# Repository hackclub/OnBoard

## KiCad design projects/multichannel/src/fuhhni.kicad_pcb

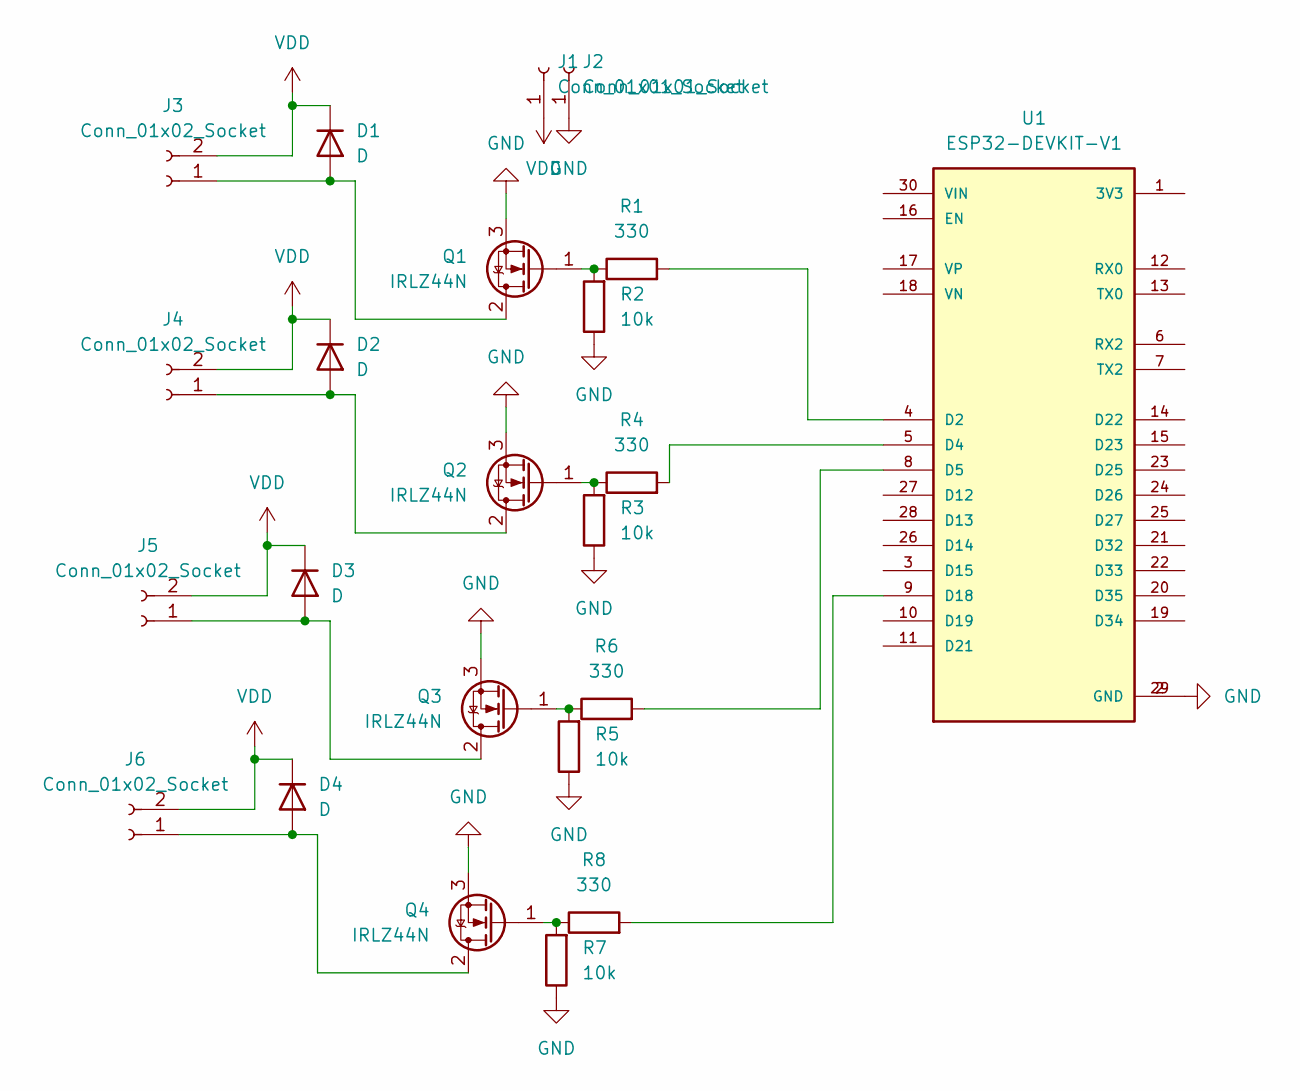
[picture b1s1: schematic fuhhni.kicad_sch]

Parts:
D1, D2, D3, D4: D; D_A-405_P7.62mm_Horizontal
J1, J2: Conn_01x01_Socket; PinSocket_1x01_P2.54mm_Vertical
J3, J4, J5, J6: Conn_01x02_Socket; PinSocket_1x02_P2.54mm_Vertical
Q1, Q2, Q3, Q4: IRLZ44N; TO-220-3_Vertical
R1, R4, R6, R8: 330; R_Axial_DIN0207_L6.3mm_D2.5mm_P7.62mm_Horizontal
R2, R3, R5, R7: 10k; R_Axial_DIN0207_L6.3mm_D2.5mm_P7.62mm_Horizontal
U1: ESP32-DEVKIT-V1; MODULE_ESP32_DEVKIT_V1; PARTREV N/A

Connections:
GND: J2.1, Q1.3 (S), Q2.3 (S), Q3.3 (S), Q4.3 (S), R2.1, R3.1, R5.1, R7.1, U1.2 (GND), U1.29 (GND)
unnamed: D1.2 (A), J3.1, Q1.2 (D)
unnamed: D2.2 (A), J4.1, Q2.2 (D)
unnamed: D3.2 (A), J5.1, Q3.2 (D)
unnamed: D4.2 (A), J6.1, Q4.2 (D)
unnamed: Q1.1 (G), R1.1, R2.2
unnamed: Q2.1 (G), R3.2, R4.1
unnamed: Q3.1 (G), R5.2, R6.1
unnamed: Q4.1 (G), R7.2, R8.1
unnamed: R1.2, U1.4 (D2)
unnamed: R4.2, U1.5 (D4)
unnamed: R6.2, U1.8 (D5)
unnamed: R8.2, U1.9 (D18)
VDD: D1.1 (K), D2.1 (K), D3.1 (K), D4.1 (K), J1.1, J3.2, J4.2, J5.2, J6.2

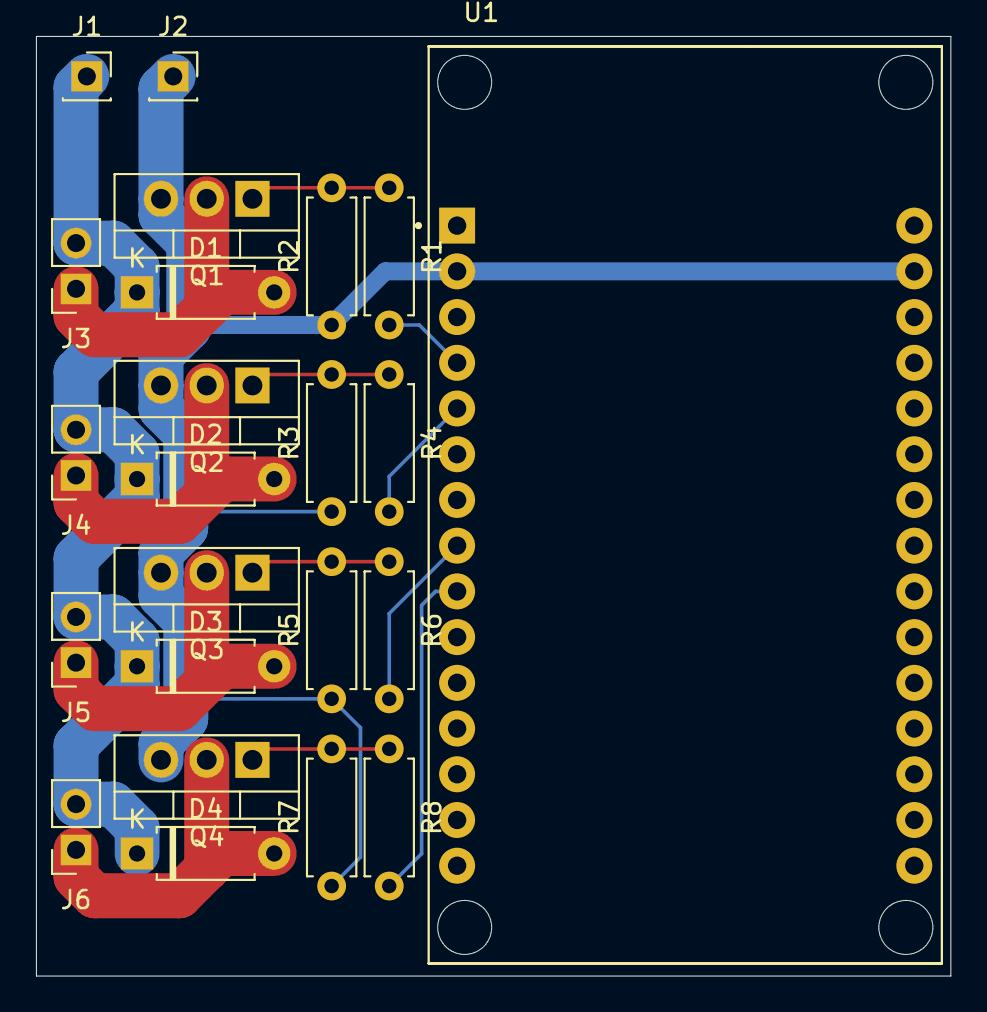
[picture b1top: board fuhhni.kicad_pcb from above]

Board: 2 copper layers, 50.8 x 52.2 mm, 23 parts (0 on the bottom side), 14 nets.

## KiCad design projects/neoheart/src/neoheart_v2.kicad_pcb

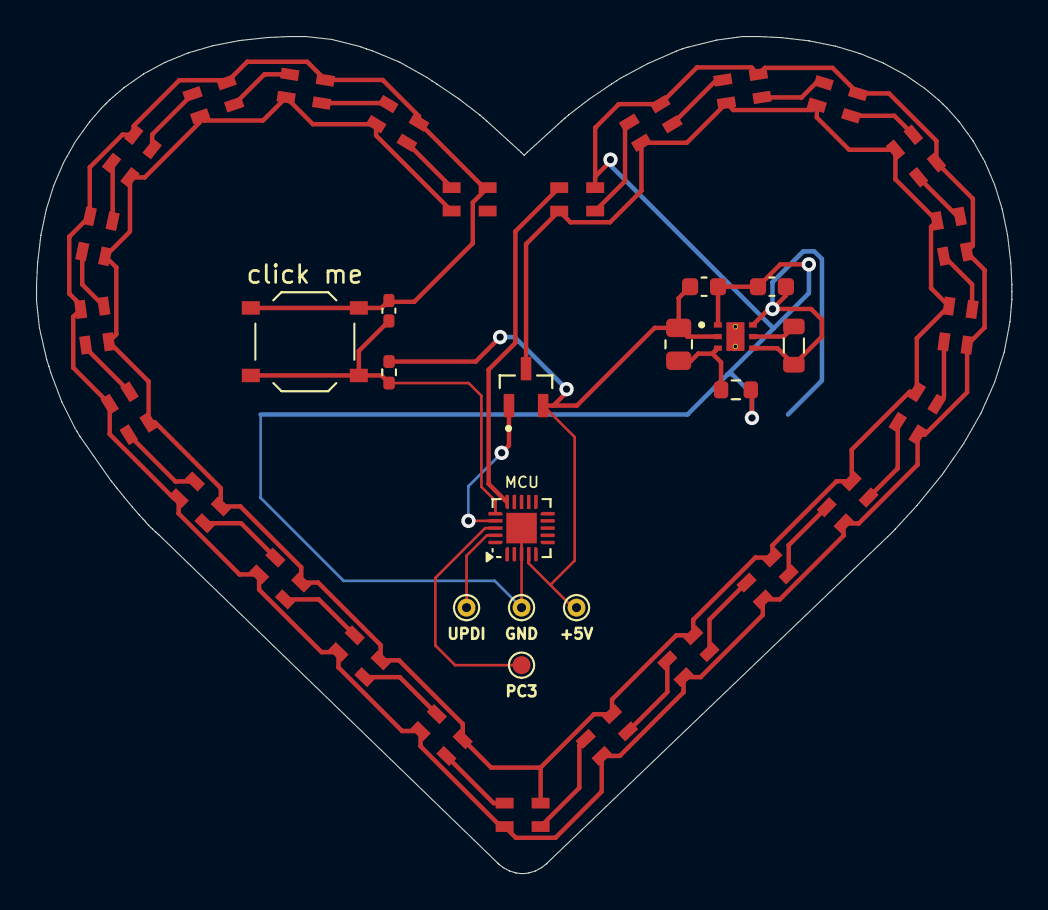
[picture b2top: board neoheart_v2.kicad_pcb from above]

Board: 2 copper layers, 54.2 x 46.5 mm, 41 parts (1 on the bottom side), 35 nets.

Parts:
+5V: +5V; TestPoint_THTPad_D1.0mm_Drill0.5mm
BATTERY (CR2032): Battery; BatteryHolder_Keystone_1060_1x2032
C2: 100nF; C_0402_1005Metric_Pad0.74x0.62mm_HandSolder
C3, C4: 22μF; C_0603_1608Metric
D1, D2, D3, D4, D5, D6, D7, D8, D9, D10, D11, D12, D13, D14, D15, D16, D17, D18, D19, D20, D21, D22, D23, D24, D25: SK6805; LED_SK6805_PLCC4_2.4x2.7mm_P1.3mm
GND: GND; TestPoint_THTPad_D1.0mm_Drill0.5mm
L1: 4,7μH; L_0805_2012Metric
MCU: ATtiny816-M; VQFN-20-1EP_3x3mm_P0.4mm_EP1.7x1.7mm
PC3: PC3; TestPoint_Pad_D1.0mm
Q1: IRLML2502; SOT95P237X112-3N
R1: 1K; R_0402_1005Metric_Pad0.72x0.64mm_HandSolder
R2: 180kΩ; R_0805_2012Metric
R3: 1,5MΩ; R_0603_1608Metric
U2: TPS61240TDRVRQ1; SON65P200X200X80-7N
UPDI: UPDI; TestPoint_THTPad_D1.0mm_Drill0.5mm
click me: SW_SPST; SW_Push_1P1T_XKB_TS-1187A

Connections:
+3V0: BATTERY (CR2032).1 (+), C3.1, L1.1, U2.4 (EN), U2.6 (VIN)
+5V: +5V.1, C4.1, MCU.4 (VCC), Q1.2, R1.1, R2.2, U2.2 (VOUT)
/IO_LEDS: D1.3 (DIN), MCU.15 (PC0)
/IO_MOSFET: MCU.17 (PC2), Q1.1
/LED5V: D1.4 (VDD), D2.4 (VDD), D3.4 (VDD), D4.4 (VDD), D5.4 (VDD), D6.4 (VDD), D7.4 (VDD), D8.4 (VDD), D9.4 (VDD), D10.4 (VDD), D11.4 (VDD), D12.4 (VDD), D13.4 (VDD), D14.4 (VDD), D15.4 (VDD), D16.4 (VDD), D17.4 (VDD), D18.4 (VDD), D19.4 (VDD), D20.4 (VDD), D21.4 (VDD), D22.4 (VDD), D23.4 (VDD), D24.4 (VDD), D25.4 (VDD), Q1.3
/PC3: MCU.18 (PC3), PC3.1
/SW_ANIM: C2.1, MCU.16 (PC1), R1.2, click me.2 (B)
/UPDI: MCU.19 (~RESET/PA0), UPDI.1
GND: BATTERY (CR2032).2 (-), C2.2, C3.2, C4.2, D1.2 (VSS), D2.2 (VSS), D3.2 (VSS), D4.2 (VSS), D5.2 (VSS), D6.2 (VSS), D7.2 (VSS), D8.2 (VSS), D9.2 (VSS), D10.2 (VSS), D11.2 (VSS), D12.2 (VSS), D13.2 (VSS), D14.2 (VSS), D15.2 (VSS), D16.2 (VSS), D17.2 (VSS), D18.2 (VSS), D19.2 (VSS), D20.2 (VSS), D21.2 (VSS), D22.2 (VSS), D23.2 (VSS), D24.2 (VSS), D25.2 (VSS), GND.1, MCU.3 (GND), MCU.21 (GND), R3.1, U2.1 (GND), click me.1 (A)
unnamed: D1.1 (DOUT), D4.3 (DIN)
unnamed: D2.3 (DIN), D24.1 (DOUT)
unnamed: D2.1 (DOUT), D5.3 (DIN)
unnamed: D3.1 (DOUT), D6.3 (DIN)
unnamed: D4.1 (DOUT), D7.3 (DIN)
unnamed: D5.1 (DOUT), D8.3 (DIN)
unnamed: D6.1 (DOUT), D9.3 (DIN)
unnamed: D7.1 (DOUT), D10.3 (DIN)
unnamed: D10.1 (DOUT), D13.3 (DIN)
unnamed: D8.1 (DOUT), D11.3 (DIN)
unnamed: D11.1 (DOUT), D14.3 (DIN)
unnamed: D9.1 (DOUT), D12.3 (DIN)
unnamed: D12.1 (DOUT), D15.3 (DIN)
unnamed: D13.1 (DOUT), D16.3 (DIN)
unnamed: D14.1 (DOUT), D17.3 (DIN)
unnamed: D16.1 (DOUT), D18.3 (DIN)
unnamed: D17.1 (DOUT), D19.3 (DIN)
unnamed: D18.1 (DOUT), D20.3 (DIN)
unnamed: D19.1 (DOUT), D21.3 (DIN)
unnamed: D20.1 (DOUT), D22.3 (DIN)
unnamed: D21.1 (DOUT), D23.3 (DIN)
unnamed: D22.1 (DOUT), D24.3 (DIN)
unnamed: D23.1 (DOUT), D25.3 (DIN)
unnamed: D3.3 (DIN), D25.1 (DOUT)
unnamed: R2.1, R3.2, U2.3 (FB)
unnamed: L1.2, U2.5 (L)

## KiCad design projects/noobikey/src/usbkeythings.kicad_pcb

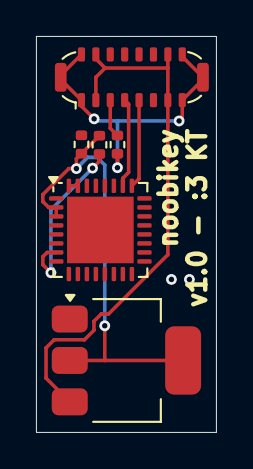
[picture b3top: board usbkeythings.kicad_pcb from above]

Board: 2 copper layers, 10.0 x 22.0 mm, 6 parts (0 on the bottom side), 8 nets.

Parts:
P1: USB_C_Plug_USB2.0; USB_C_Plug_ShenzhenJingTuoJin_918-118A2021Y40002_Vertical
R1: 5.1; R_0402_1005Metric
R2, R3: 10; R_0402_1005Metric
U1: ESP32-C3; QFN-32-1EP_5x5mm_P0.5mm_EP3.7x3.7mm
U2: AMS1117-3.3; SOT-223-3_TabPin2

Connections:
+3.3V: R2.2, R3.1, U1.2 (VDD3P3), U1.3 (VDD3P3), U2.2 (VO)
GND: P1.A1 (GND), P1.A12 (GND), P1.B1 (GND), P1.B12 (GND), P1.S1 (SHIELD), R1.1, U1.33 (GND)
unnamed: P1.A5 (CC), R1.2
unnamed: P1.A6 (D+), U1.26 (GPIO19)
unnamed: P1.A7 (D-), U1.25 (GPIO18)
unnamed: R2.1, U1.7 (CHIP_EN)
unnamed: U1.31 (VDDA), U1.32 (VDDA)
unnamed: P1.A4 (VBUS), P1.A9 (VBUS), P1.B4 (VBUS), P1.B9 (VBUS), U2.3 (VI)

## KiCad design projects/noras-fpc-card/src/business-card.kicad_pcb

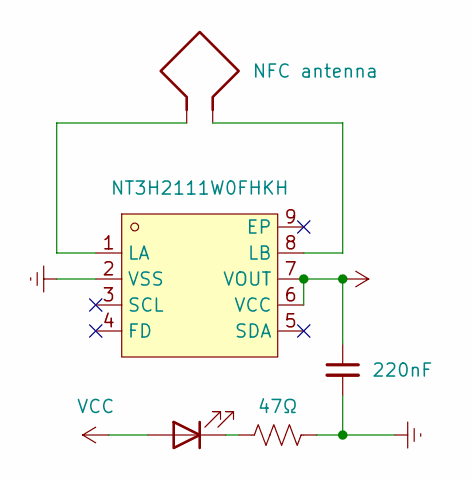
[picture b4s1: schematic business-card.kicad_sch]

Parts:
AE1: NFC antenna; nfc_ant
C1: 220nF; C_0603_1608Metric_Pad1.08x0.95mm_HandSolder
D1: LED; LED_0603_1608Metric_Pad1.05x0.95mm_HandSolder
R1: 47Ω; R_0603_1608Metric_Pad0.98x0.95mm_HandSolder
U1: NT3H2111W0FHKH; XQFN-8_L1.6-W1.6-P0.50-BL; LCSC Part C710403

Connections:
GND: C1.2, R1.2, U1.2 (VSS)
unnamed: D1.1 (K), R1.1
unnamed: AE1.1, U1.1 (LA)
unnamed: AE1.2, U1.8 (LB)
VCC: C1.1, D1.2 (A), U1.6 (VCC), U1.7 (VOUT)

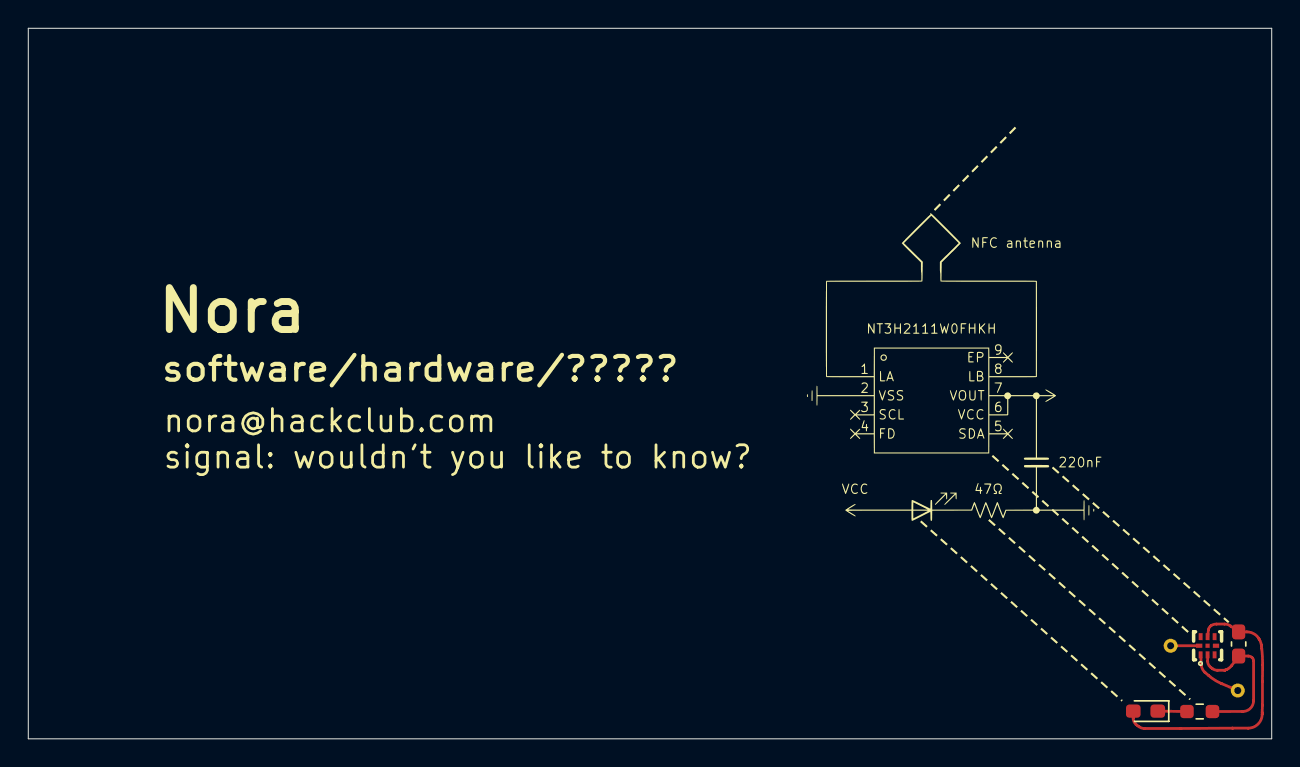
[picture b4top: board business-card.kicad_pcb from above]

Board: 2 copper layers, 88.9 x 50.8 mm, 5 parts (1 on the bottom side), 5 nets.

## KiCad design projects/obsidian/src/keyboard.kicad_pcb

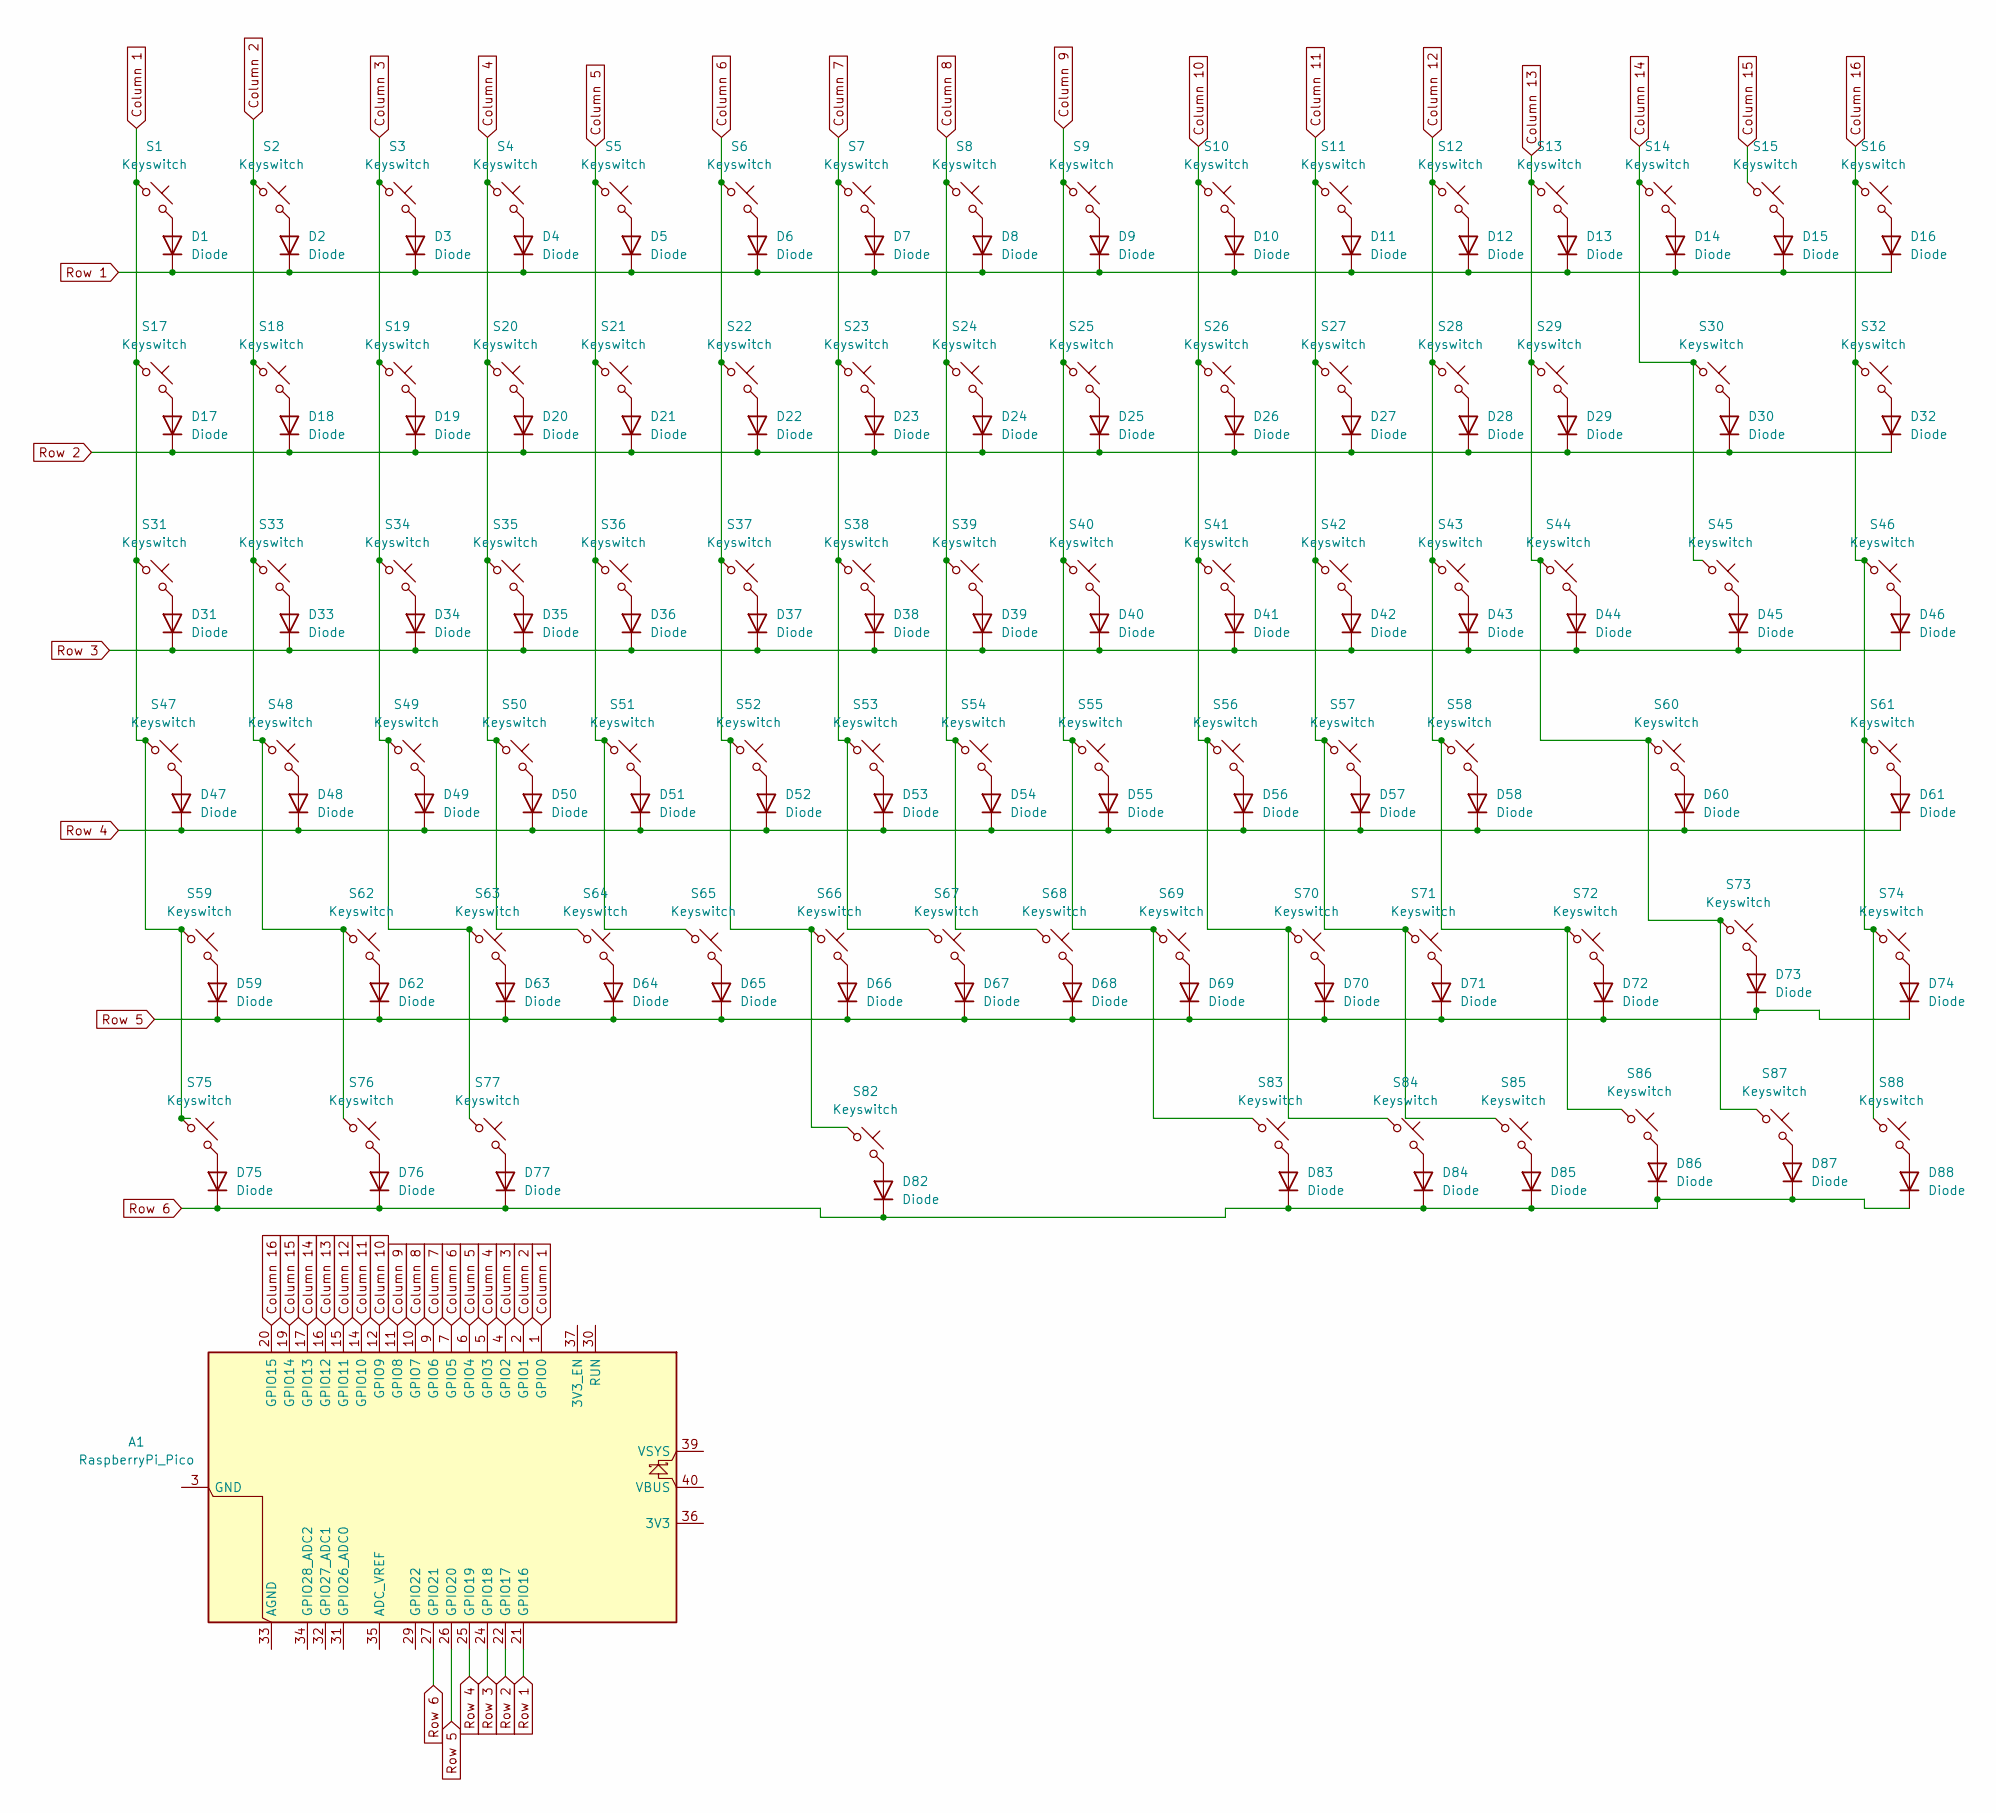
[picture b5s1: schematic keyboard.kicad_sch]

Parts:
A1: RaspberryPi_Pico; RaspberryPi_Pico_Common_THT
D1, D2, D3, D4, D5, D6, D7, D8, D9, D10, D11, D12, D13, D14, D15, D16, D17, D18, D19, D20, D21, D22, D23, D24, D25, D26, D27, D28, D29, D30, D31, D32, D33, D34, D35, D36, D37, D38, D39, D40, D41, D42, D43, D44, D45, D46, D47, D48, D49, D50, D51, D52, D53, D54, D55, D56, D57, D58, D59, D60, D61, D62, D63, D64, D65, D66, D67, D68, D69, D70, D71, D72, D73, D74, D75, D76, D77, D82, D83, D84, D85, D86, D87, D88: Diode; Diode_DO-35
S1, S2, S3, S4, S5, S6, S7, S8, S9, S10, S11, S12, S13, S14, S15, S16, S17, S18, S19, S20, S21, S22, S23, S24, S25, S26, S27, S28, S29, S32, S33, S34, S35, S36, S37, S38, S39, S40, S41, S42, S43, S44, S46, S48, S49, S50, S51, S52, S53, S54, S55, S56, S57, S58, S61, S62, S63, S64, S65, S66, S67, S68, S69, S70, S71, S73, S74, S83, S84, S85, S86, S87, S88: Keyswitch; Hotswap_MX_1.00u
S30: Keyswitch; Hotswap_MX_2.00u
S31, S45: Keyswitch; Hotswap_MX_1.50u
S47, S72: Keyswitch; Hotswap_MX_1.75u
S59, S60: Keyswitch; Hotswap_MX_2.25u
S75, S76, S77: Keyswitch; Hotswap_MX_1.25u
S82: Keyswitch; Hotswap_MX_6.25u

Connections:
Column 1: A1.1 (GPIO0), S1.1, S17.1, S31.1, S47.1, S59.1, S75.1
Column 2: A1.2 (GPIO1), S2.1, S18.1, S33.1, S48.1, S62.1, S76.1
Column 3: A1.4 (GPIO2), S3.1, S19.1, S34.1, S49.1, S63.1, S77.1
Column 4: A1.5 (GPIO3), S4.1, S20.1, S35.1, S50.1, S64.1
Column 5: A1.6 (GPIO4), S5.1, S21.1, S36.1, S51.1, S65.1
Column 6: A1.7 (GPIO5), S6.1, S22.1, S37.1, S52.1, S66.1, S82.1
Column 7: A1.9 (GPIO6), S7.1, S23.1, S38.1, S53.1, S67.1
Column 8: A1.10 (GPIO7), S8.1, S24.1, S39.1, S54.1, S68.1
Column 9: A1.11 (GPIO8), S9.1, S25.1, S40.1, S55.1, S69.1, S83.1
Column 10: A1.12 (GPIO9), S10.1, S26.1, S41.1, S56.1, S70.1, S84.1
Column 11: A1.14 (GPIO10), S11.1, S27.1, S42.1, S57.1, S71.1, S85.1
Column 12: A1.15 (GPIO11), S12.1, S28.1, S43.1, S58.1, S72.1, S86.1
Column 13: A1.16 (GPIO12), S13.1, S29.1, S44.1, S60.1, S73.1, S87.1
Column 14: A1.17 (GPIO13), S14.1, S30.1, S45.1
Column 15: A1.19 (GPIO14), S15.1
Column 16: A1.20 (GPIO15), S16.1, S32.1, S46.1, S61.1, S74.1, S88.1
unnamed: A1.3 (GND), A1.8 (GND), A1.13 (GND), A1.18 (GND), A1.23 (GND), A1.28 (GND), A1.38 (GND)
unnamed: D1.2 (A), S1.2
unnamed: D2.2 (A), S2.2
unnamed: D3.2 (A), S3.2
unnamed: D4.2 (A), S4.2
unnamed: D5.2 (A), S5.2
unnamed: D6.2 (A), S6.2
unnamed: D7.2 (A), S7.2
unnamed: D8.2 (A), S8.2
unnamed: D9.2 (A), S9.2
unnamed: D10.2 (A), S10.2
unnamed: D11.2 (A), S11.2
unnamed: D12.2 (A), S12.2
unnamed: D13.2 (A), S13.2
unnamed: D14.2 (A), S14.2
unnamed: D15.2 (A), S15.2
unnamed: D16.2 (A), S16.2
unnamed: D17.2 (A), S17.2
unnamed: D18.2 (A), S18.2
unnamed: D19.2 (A), S19.2
unnamed: D20.2 (A), S20.2
unnamed: D21.2 (A), S21.2
unnamed: D22.2 (A), S22.2
unnamed: D23.2 (A), S23.2
unnamed: D24.2 (A), S24.2
unnamed: D25.2 (A), S25.2
unnamed: D26.2 (A), S26.2
unnamed: D27.2 (A), S27.2
unnamed: D28.2 (A), S28.2
unnamed: D29.2 (A), S29.2
unnamed: D30.2 (A), S30.2
unnamed: D31.2 (A), S31.2
unnamed: D32.2 (A), S32.2
unnamed: D33.2 (A), S33.2
unnamed: D34.2 (A), S34.2
unnamed: D35.2 (A), S35.2
unnamed: D36.2 (A), S36.2
unnamed: D37.2 (A), S37.2
unnamed: D38.2 (A), S38.2
unnamed: D39.2 (A), S39.2
unnamed: D40.2 (A), S40.2
unnamed: D41.2 (A), S41.2
unnamed: D42.2 (A), S42.2
unnamed: D43.2 (A), S43.2
unnamed: D44.2 (A), S44.2
unnamed: D45.2 (A), S45.2
unnamed: D46.2 (A), S46.2
unnamed: D47.2 (A), S47.2
unnamed: D48.2 (A), S48.2
unnamed: D49.2 (A), S49.2
unnamed: D50.2 (A), S50.2
unnamed: D51.2 (A), S51.2
unnamed: D52.2 (A), S52.2
unnamed: D53.2 (A), S53.2
unnamed: D54.2 (A), S54.2
unnamed: D55.2 (A), S55.2
unnamed: D56.2 (A), S56.2
unnamed: D57.2 (A), S57.2
unnamed: D58.2 (A), S58.2
unnamed: D59.2 (A), S59.2
unnamed: D60.2 (A), S60.2
unnamed: D61.2 (A), S61.2
unnamed: D62.2 (A), S62.2
unnamed: D63.2 (A), S63.2
unnamed: D64.2 (A), S64.2
unnamed: D65.2 (A), S65.2
unnamed: D66.2 (A), S66.2
unnamed: D67.2 (A), S67.2
unnamed: D68.2 (A), S68.2
unnamed: D69.2 (A), S69.2
unnamed: D70.2 (A), S70.2
unnamed: D71.2 (A), S71.2
unnamed: D72.2 (A), S72.2
unnamed: D73.2 (A), S73.2
unnamed: D74.2 (A), S74.2
unnamed: D75.2 (A), S75.2
unnamed: D76.2 (A), S76.2
unnamed: D77.2 (A), S77.2
unnamed: D82.2 (A), S82.2
unnamed: D83.2 (A), S83.2
unnamed: D84.2 (A), S84.2
unnamed: D85.2 (A), S85.2
unnamed: D86.2 (A), S86.2
unnamed: D87.2 (A), S87.2
unnamed: D88.2 (A), S88.2
Row 1: A1.21 (GPIO16), D1.1 (K), D2.1 (K), D3.1 (K), D4.1 (K), D5.1 (K), D6.1 (K), D7.1 (K), D8.1 (K), D9.1 (K), D10.1 (K), D11.1 (K), D12.1 (K), D13.1 (K), D14.1 (K), D15.1 (K), D16.1 (K)
Row 2: A1.22 (GPIO17), D17.1 (K), D18.1 (K), D19.1 (K), D20.1 (K), D21.1 (K), D22.1 (K), D23.1 (K), D24.1 (K), D25.1 (K), D26.1 (K), D27.1 (K), D28.1 (K), D29.1 (K), D30.1 (K), D32.1 (K)
Row 3: A1.24 (GPIO18), D31.1 (K), D33.1 (K), D34.1 (K), D35.1 (K), D36.1 (K), D37.1 (K), D38.1 (K), D39.1 (K), D40.1 (K), D41.1 (K), D42.1 (K), D43.1 (K), D44.1 (K), D45.1 (K), D46.1 (K)
Row 4: A1.25 (GPIO19), D47.1 (K), D48.1 (K), D49.1 (K), D50.1 (K), D51.1 (K), D52.1 (K), D53.1 (K), D54.1 (K), D55.1 (K), D56.1 (K), D57.1 (K), D58.1 (K), D60.1 (K), D61.1 (K)
Row 5: A1.26 (GPIO20), D59.1 (K), D62.1 (K), D63.1 (K), D64.1 (K), D65.1 (K), D66.1 (K), D67.1 (K), D68.1 (K), D69.1 (K), D70.1 (K), D71.1 (K), D72.1 (K), D73.1 (K), D74.1 (K)
Row 6: A1.27 (GPIO21), D75.1 (K), D76.1 (K), D77.1 (K), D82.1 (K), D83.1 (K), D84.1 (K), D85.1 (K), D86.1 (K), D87.1 (K), D88.1 (K)

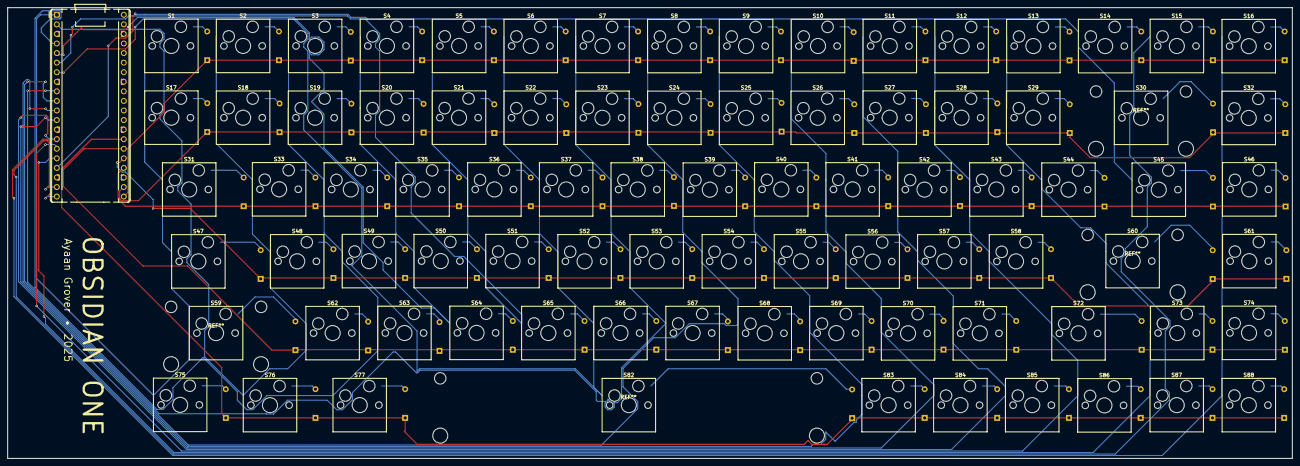
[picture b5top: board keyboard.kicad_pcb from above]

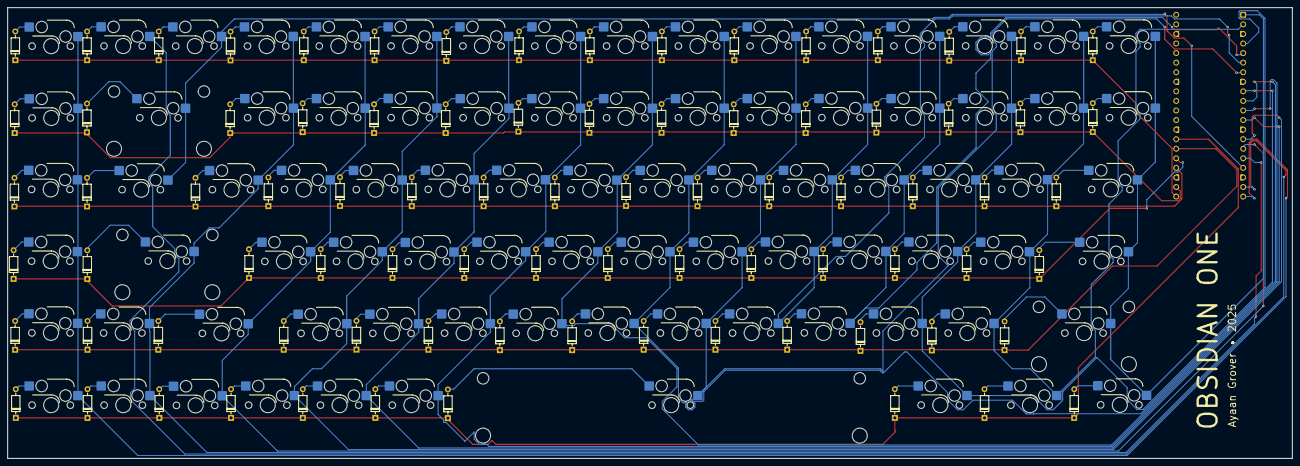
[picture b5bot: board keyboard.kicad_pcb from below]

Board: 2 copper layers, 341.1 x 119.7 mm, 169 parts (84 on the bottom side), 107 nets.

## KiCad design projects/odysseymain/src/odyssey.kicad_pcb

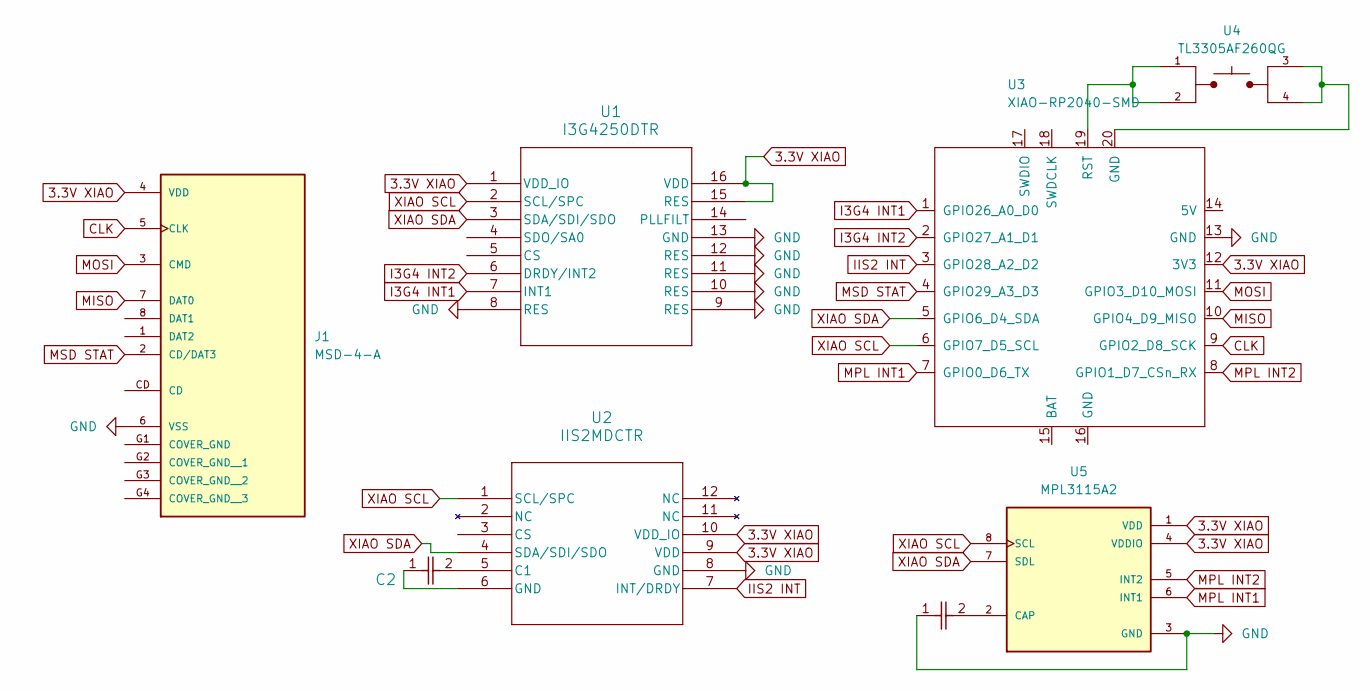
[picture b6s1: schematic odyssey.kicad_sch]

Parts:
C1: 0402B104K160CT; CAP_0402_N_WAL
C3: C2; CAP_0402_N_WAL
J1: MSD-4-A; CUI_MSD-4-A; PARTREV 1.0
U1: I3G4250DTR
U2: IIS2MDCTR
U3: XIAO-RP2040-SMD
U4: TL3305AF260QG; SW_TL3305AF260QG; PARTREV C
U5: MPL3115A2; NXP_LGA-8_3x5mm_P1.25mm_H1.1mm

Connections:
3.3V XIAO: J1.4 (VDD), U1.1 (VDD_IO), U1.15 (RES), U1.16 (VDD), U2.9 (VDD), U2.10 (VDD_IO), U3.12 (3V3), U5.1 (VDD), U5.4 (VDDIO)
CLK: J1.5 (CLK), U3.9 (GPIO2_D8_SCK)
GND: C1.1, J1.6 (VSS), U1.8 (RES), U1.9 (RES), U1.10 (RES), U1.11 (RES), U1.12 (RES), U1.13 (GND), U2.8 (GND), U3.13 (GND), U5.3 (GND)
I3G4 INT1: U1.7 (INT1), U3.1 (GPIO26_A0_D0)
I3G4 INT2: U1.6 (DRDY/INT2), U3.2 (GPIO27_A1_D1)
IIS2 INT: U2.7 (INT/DRDY), U3.3 (GPIO28_A2_D2)
MISO: J1.7 (DAT0), U3.10 (GPIO4_D9_MISO)
MOSI: J1.3 (CMD), U3.11 (GPIO3_D10_MOSI)
MPL INT1: U3.7 (GPIO0_D6_TX), U5.6 (INT1)
MPL INT2: U3.8 (GPIO1_D7_CSn_RX), U5.5 (INT2)
MSD STAT: J1.2 (CD/DAT3), U3.4 (GPIO29_A3_D3)
unnamed: C3.1, U2.6 (GND)
unnamed: C3.2, U2.5 (C1)
unnamed: U3.20 (GND), U4.3, U4.4
unnamed: U3.19 (RST), U4.1, U4.2
unnamed: C1.2, U5.2 (CAP)
XIAO SCL: U1.2 (SCL/SPC), U2.1 (SCL/SPC), U3.6 (GPIO7_D5_SCL), U5.8 (SCL)
XIAO SDA: U1.3 (SDA/SDI/SDO), U2.4 (SDA/SDI/SDO), U3.5 (GPIO6_D4_SDA), U5.7 (SDL)

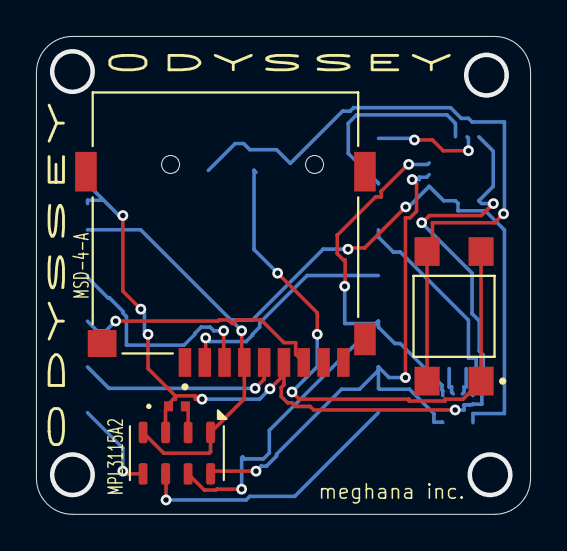
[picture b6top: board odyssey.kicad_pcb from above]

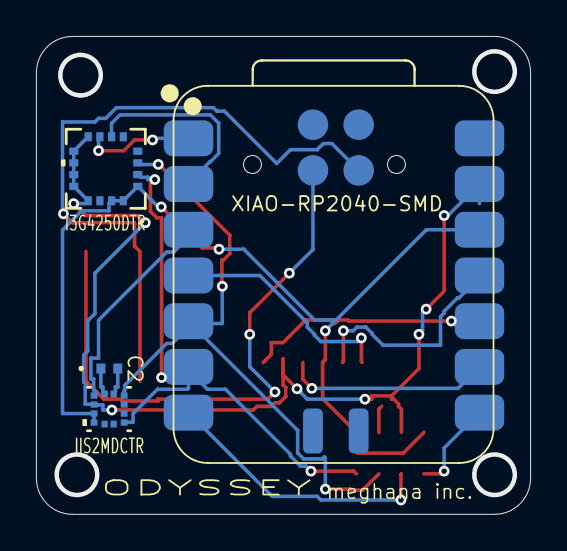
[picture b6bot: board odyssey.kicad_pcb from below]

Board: 2 copper layers, 27.5 x 26.5 mm, 8 parts (4 on the bottom side), 18 nets.

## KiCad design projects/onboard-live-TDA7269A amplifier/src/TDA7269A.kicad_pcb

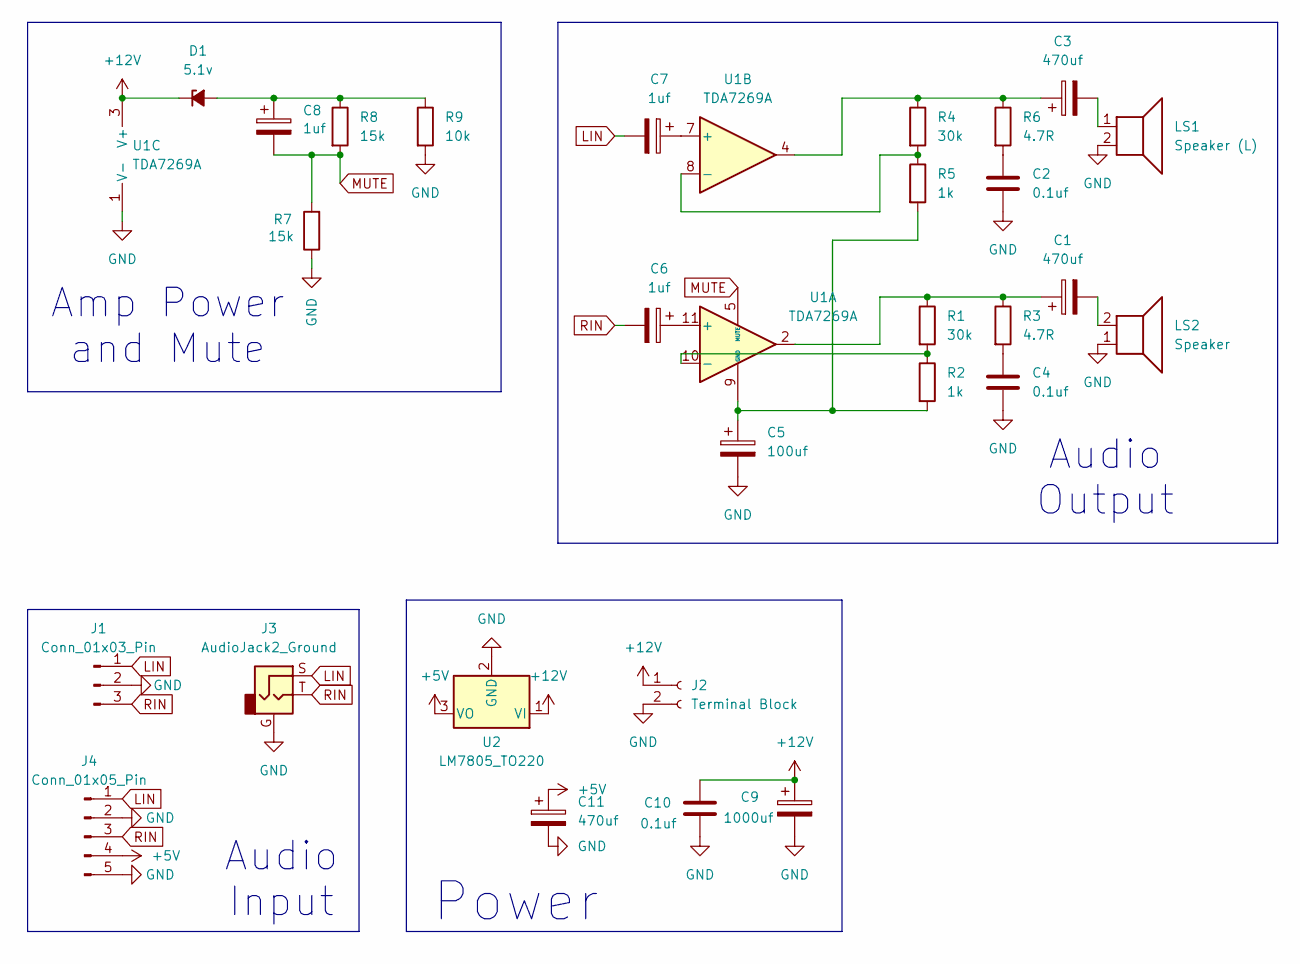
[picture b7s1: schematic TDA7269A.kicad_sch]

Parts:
C1, C3, C11: 470uf; CP_Radial_D8.0mm_P3.50mm
C2, C4, C10: 0.1uf; C_Disc_D7.0mm_W2.5mm_P5.00mm
C5: 100uf; CP_Radial_D6.3mm_P2.50mm
C6, C7, C8: 1uf; CP_Radial_D5.0mm_P2.50mm
C9: 1000uf; CP_Radial_D13.0mm_P5.00mm
D1: 5.1v; D_DO-35_SOD27_P7.62mm_Horizontal
J1: Conn_01x03_Pin; JST_XH_B3B-XH-AM_1x03_P2.50mm_Vertical
J2: Terminal Block; TerminalBlock_Phoenix_MKDS-1,5-2-5.08_1x02_P5.08mm_Horizont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
J3: AudioJack2_Ground; PJ-3200
J4: Conn_01x05_Pin; PinHeader_1x05_P2.54mm_Vertical
LS1: Speaker (L); TerminalBlock_Phoenix_MKDS-1,5-2-5.08_1x02_P5.08mm_Horizont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
LS2: Speaker; TerminalBlock_Phoenix_MKDS-1,5-2-5.08_1x02_P5.08mm_Horizont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
R1, R4: 30k; R_Axial_DIN0207_L6.3mm_D2.5mm_P7.62mm_Horizontal
R2, R5: 1k; R_Axial_DIN0207_L6.3mm_D2.5mm_P7.62mm_Horizontal
R3, R6: 4.7R; R_Axial_DIN0207_L6.3mm_D2.5mm_P7.62mm_Horizontal
R7, R8: 15k; R_Axial_DIN0207_L6.3mm_D2.5mm_P7.62mm_Horizontal
R9: 10k; R_Axial_DIN0207_L6.3mm_D2.5mm_P7.62mm_Horizontal
U1: TDA7269A; TO-220-11_P3.4x5.08mm_StaggerOdd_Lead4.85mm_Vertical
U2: LM7805_TO220; TO-220-3_Vertical

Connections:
+5V: C11.1, J4.4, U2.3 (VO)
+12V: C9.1, C10.2, D1.1 (K), J2.1, U1.3 (V+), U2.1 (VI)
GND: C2.1, C4.2, C5.2, C9.2, C10.1, C11.2, J1.2, J2.2, J3.G, J4.2, J4.5, LS1.2, LS2.1, R7.1, R9.2, U1.1 (V-), U1.6 (V-), U2.2 (GND)
LIN: C7.2, J1.1, J3.S, J4.1
MUTE: C8.2, R7.2, R8.2, U1.5 (MUTE)
unnamed: C1.1, R1.1, R3.1, U1.2
unnamed: C1.2, LS2.2
unnamed: C2.2, R6.2
unnamed: C3.1, R4.1, R6.1, U1.4
unnamed: C3.2, LS1.1
unnamed: C4.1, R3.2
unnamed: C8.1, D1.2 (A), R8.1, R9.1
unnamed: C6.1, U1.11 (+)
unnamed: R1.2, R2.1, U1.10 (-)
unnamed: C5.1, R2.2, R5.2, U1.9 (GND)
unnamed: C7.1, U1.7 (+)
unnamed: R4.2, R5.1, U1.8 (-)
RIN: C6.2, J1.3, J3.T, J4.3

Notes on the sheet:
Power
Amp Power and Mute
Audio Input
Audio Output

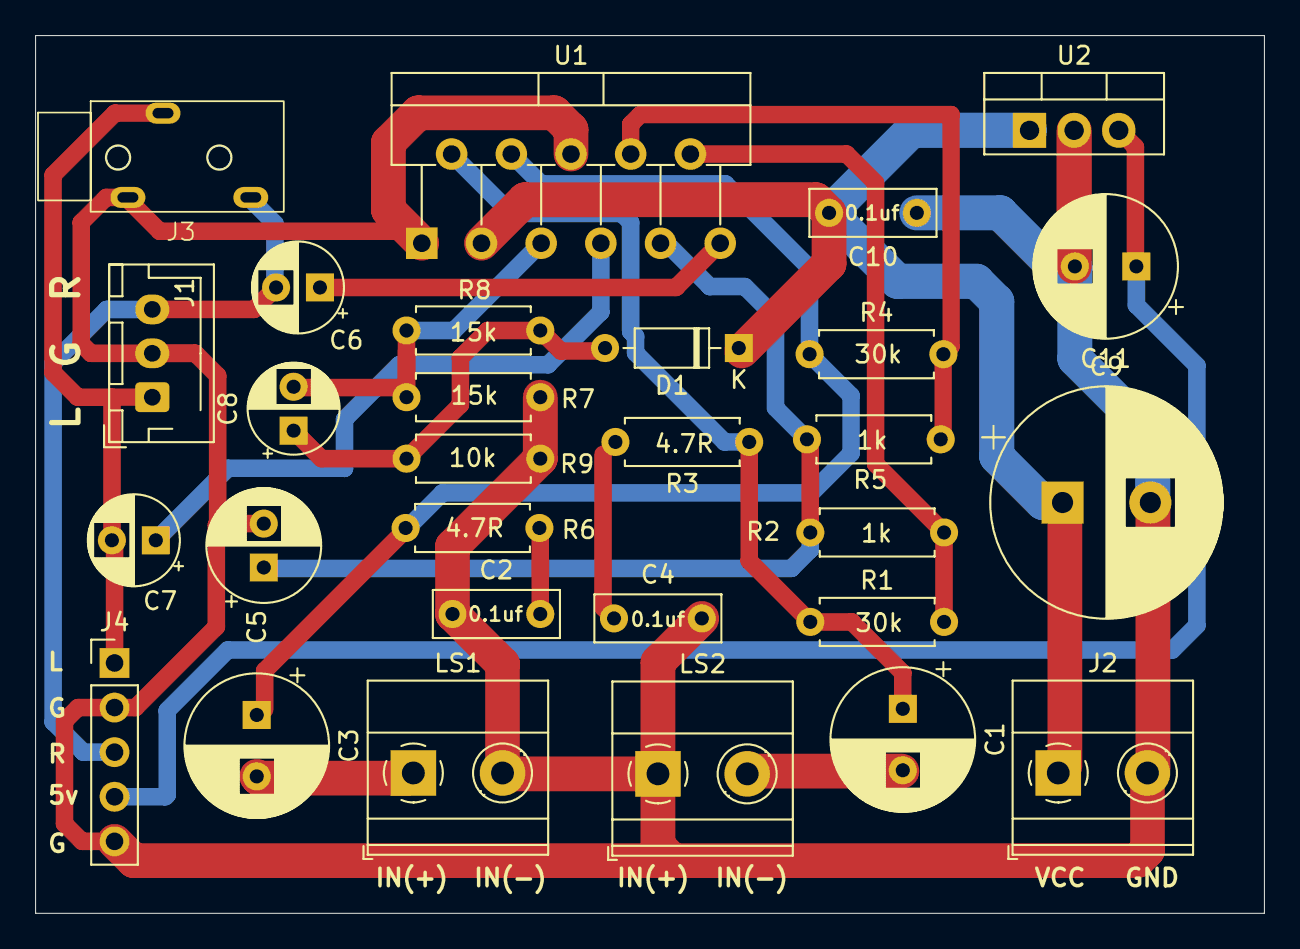
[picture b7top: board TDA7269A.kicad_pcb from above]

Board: 2 copper layers, 70.0 x 50.0 mm, 29 parts (0 on the bottom side), 18 nets.
